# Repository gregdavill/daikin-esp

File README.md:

# Daikin-ESP

Wireless A/C Controller, an ESP32-C3 based hardware module to connect to a Daikin ducted A/C system and enable WiFi control in Home Assistant.

## Hardware

The PCB repo contains a few different designs:
 - `saphire-captain` : Initial ESP32 + XL1192 board. Power extraction from the bus and transmission didn't work well.
 - `hb-bob-r0.1` : Breakout board designed for the MAX22088 homebus transceiver. This board enabled rx/tx and power from the P1P2 bus.
 - `esp-daikin-r1.0` : Basic ESP32-C3 board with DCDC, dosigned to attach directly to the hb-bob board.

## Firmware

The current firmware targets the `esp-daikin` + `hb-bob` PCB combo. Initial flashing is done with a serial connection to the ESP32-C3. Once flashed OTA updates are supported.
The firmware makes use of esphome to provide the WiFi and Home Assistant code base. A simple C++ component is used to handle the low level encoding, and protocol level decoding.

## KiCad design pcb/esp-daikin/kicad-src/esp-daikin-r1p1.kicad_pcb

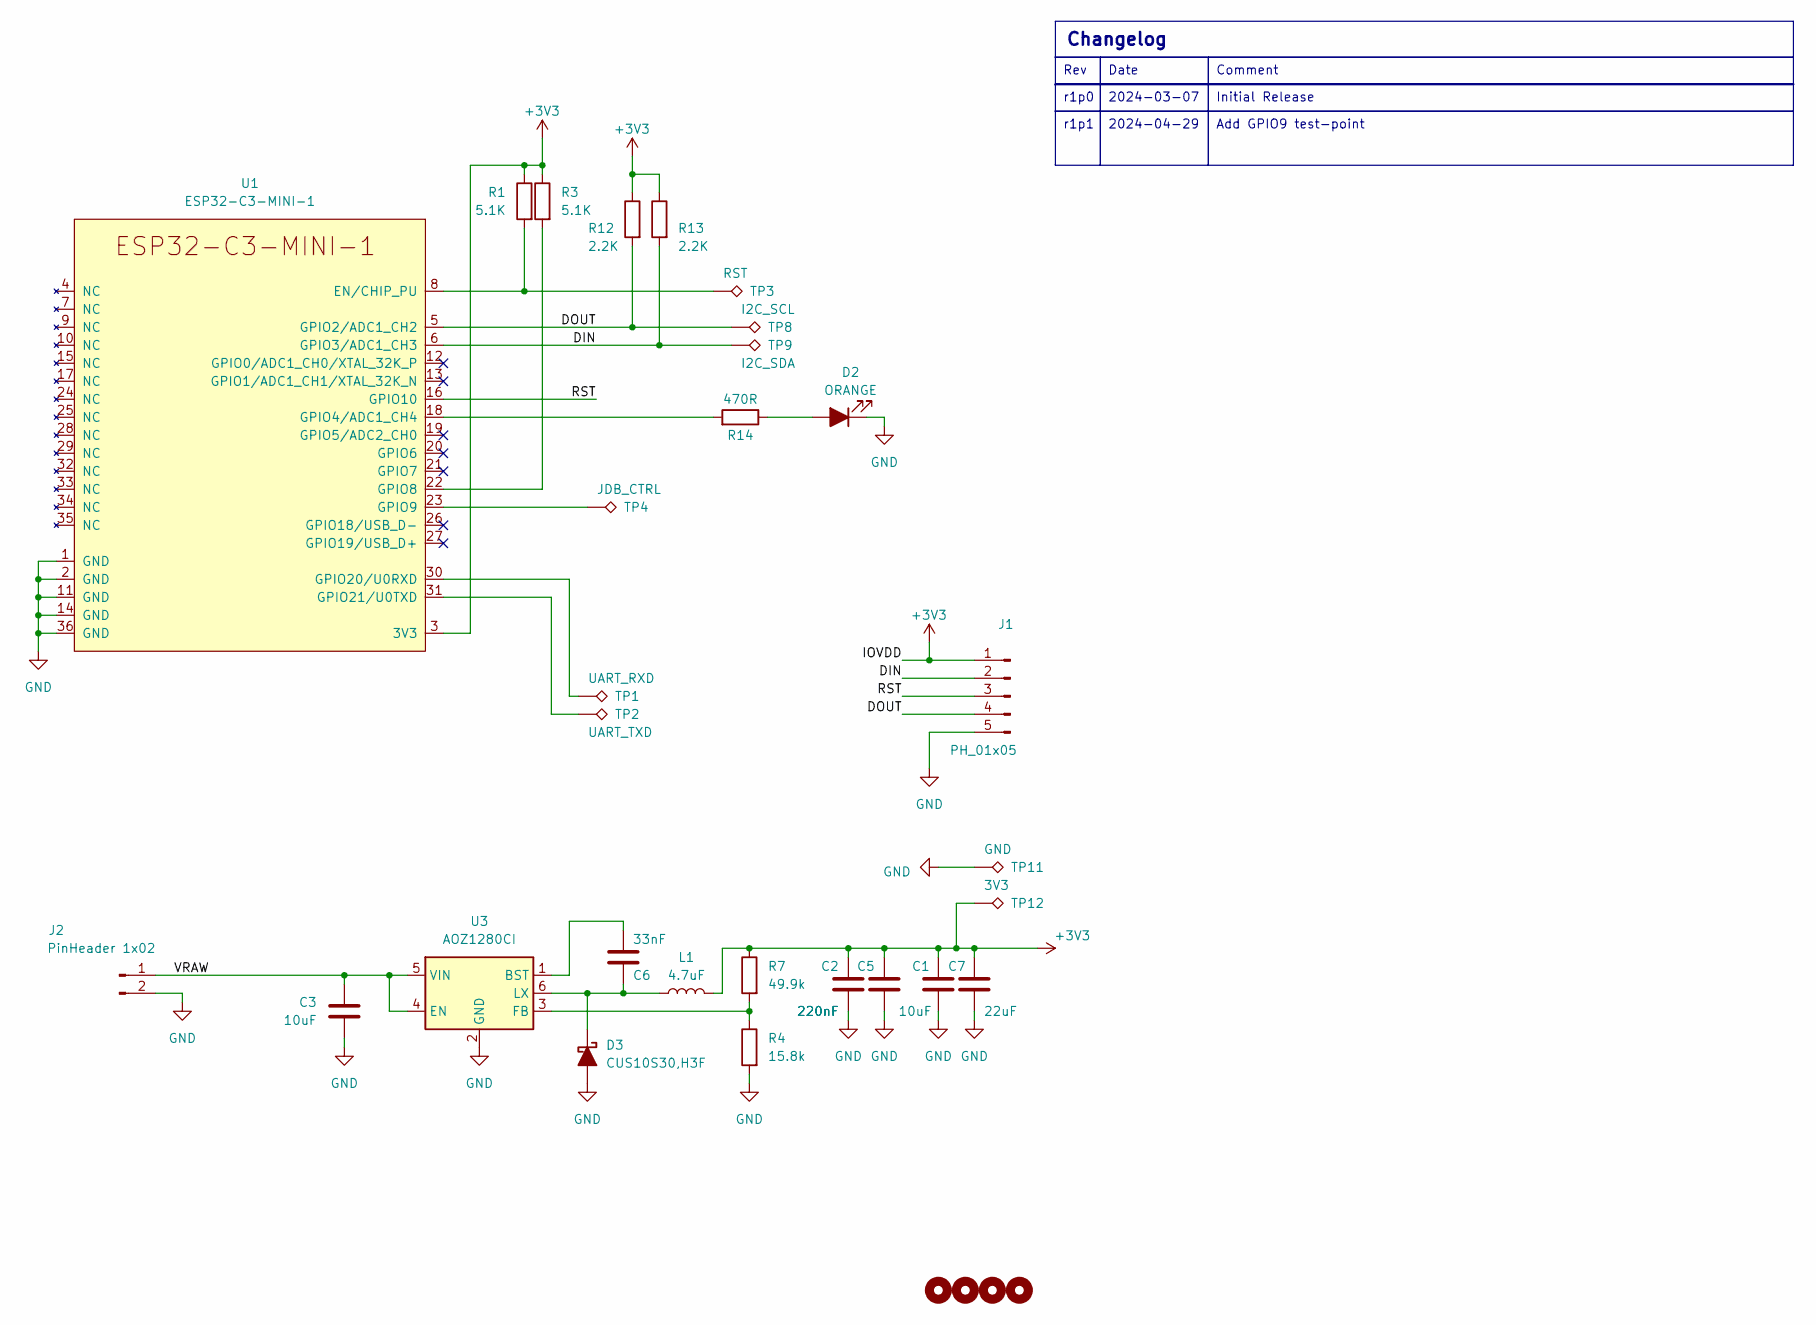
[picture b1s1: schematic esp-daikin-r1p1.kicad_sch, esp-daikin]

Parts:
C1, C3: 10uF; C_0603_1608Metric; LCSC C96446
C2, C5: 220nF; C_0402_1005Metric; LCSC C16772
C6: 33nF; C_0402_1005Metric; LCSC C106862
C7: 22uF; C_0603_1608Metric; LCSC C59461
D2: ORANGE; LED_0402_1005Metric; LCSC C965791
D3: CUS10S30,H3F; D_SOD-523; LCSC C8523
H1, H2, H3, H4: MountingHole; MountingHole_3.2mm_M3_DIN965
J1: PH_01x05; PinHeader_1x05_P2.54mm_Vertical
J2: PinHeader 1x02; PinHeader_1x02_P2.54mm_Vertical
L1: 4.7uF; L_0805_2012Metric; LCSC C63166
R1, R3: 5.1K; R_0402_1005Metric; LCSC C25905
R4: 15.8k; R_0402_1005Metric; LCSC C26956
R7: 49.9k; R_0402_1005Metric; LCSC C25897
R12, R13: 2.2K; R_0402_1005Metric; LCSC C25879
R14: 470R; R_0402_1005Metric; LCSC C25117
TP1: UART_RXD; TestPoint_Pad_D1.0mm
TP2: UART_TXD; TestPoint_Pad_D1.0mm
TP3: RST; TestPoint_Pad_D1.0mm
TP4: JDB_CTRL; TestPoint_Pad_D1.0mm
TP8: I2C_SCL; TestPoint_Pad_D1.0mm
TP9: I2C_SDA; TestPoint_Pad_D1.0mm
TP11: GND; TestPoint_Pad_D1.0mm
TP12: 3V3; TestPoint_Pad_D1.0mm
U1: ESP32-C3-MINI-1; LCSC C2934569
U3: AOZ1280CI; SOT-23-6; LCSC C41240

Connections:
+3V3: C1.1, C2.1, C5.1, C7.1, J1.1, L1.2, R1.1, R3.1, R7.1, R12.1, R13.1, TP12.1, U1.3 (3V3)
/DIN: J1.2, R13.2, TP9.1, U1.6 (GPIO3/ADC1_CH3)
/DOUT: J1.4, R12.2, TP8.1, U1.5 (GPIO2/ADC1_CH2)
/RST: J1.3, U1.16 (GPIO10)
/VRAW: C3.1, J2.1, U3.4 (EN), U3.5 (VIN)
GND: C1.2, C2.2, C3.2, C5.2, C7.2, D2.1 (K), D3.2 (A), J1.5, J2.2, R4.2, TP11.1, U1.1 (GND), U1.2 (GND), U1.11 (GND), U1.14 (GND), U1.36 (GND), U1.37 (GND), U1.38 (GND), U1.39 (GND), U1.40 (GND), U1.41 (GND), U1.42 (GND), U1.43 (GND), U1.44 (GND), U1.45 (GND), U1.46 (GND), U1.47 (GND), U1.48 (GND), U1.49 (GND), U1.50 (GND), U1.51 (GND), U1.52 (GND), U1.53 (GND), U3.2 (GND)
unnamed: D2.2 (A), R14.1
unnamed: C6.1, D3.1 (K), L1.1, U3.6 (LX)
unnamed: R1.2, TP3.1, U1.8 (EN/CHIP_PU)
unnamed: R14.2, U1.18 (GPIO4/ADC1_CH4)
unnamed: R3.2, U1.22 (GPIO8)
unnamed: TP4.1, U1.23 (GPIO9)
unnamed: TP1.1, U1.30 (GPIO20/U0RXD)
unnamed: TP2.1, U1.31 (GPIO21/U0TXD)
unnamed: C6.2, U3.1 (BST)
unnamed: R4.1, R7.2, U3.3 (FB)

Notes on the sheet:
Add GPIO9 test-point
Date
r1p0
Changelog
Rev
Comment
2024-03-07
2024-04-29
Initial Release
r1p1

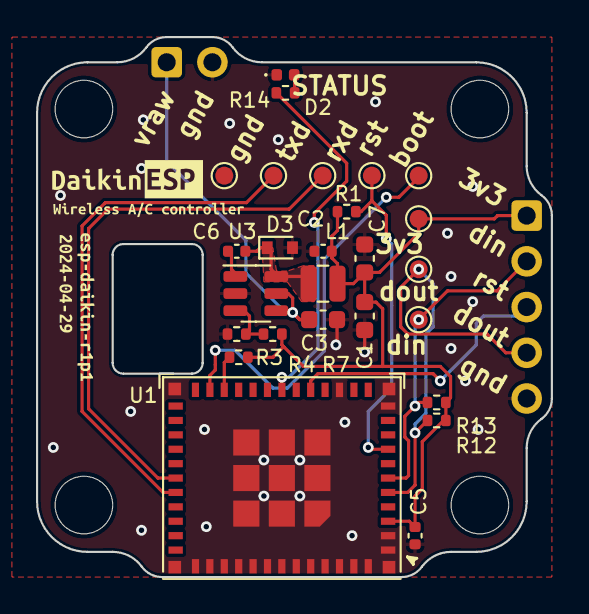
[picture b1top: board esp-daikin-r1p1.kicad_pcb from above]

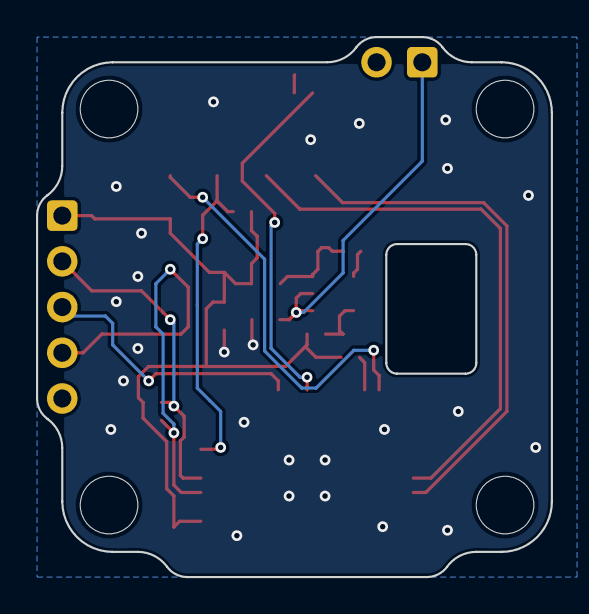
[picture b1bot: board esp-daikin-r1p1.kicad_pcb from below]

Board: 2 copper layers, 28.6 x 30.0 mm, 37 parts (6 on the bottom side), 16 nets.

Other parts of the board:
kibuzzard-65E1B0DF: G***; kibuzzard-65E1B0DF
kibuzzard-65E1B071: G***; kibuzzard-65E1B071
kibuzzard-65E1B080: G***; kibuzzard-65E1B080
kibuzzard-663027A7: G***; kibuzzard-663027A7
kibuzzard-663027CC: G***; kibuzzard-663027CC

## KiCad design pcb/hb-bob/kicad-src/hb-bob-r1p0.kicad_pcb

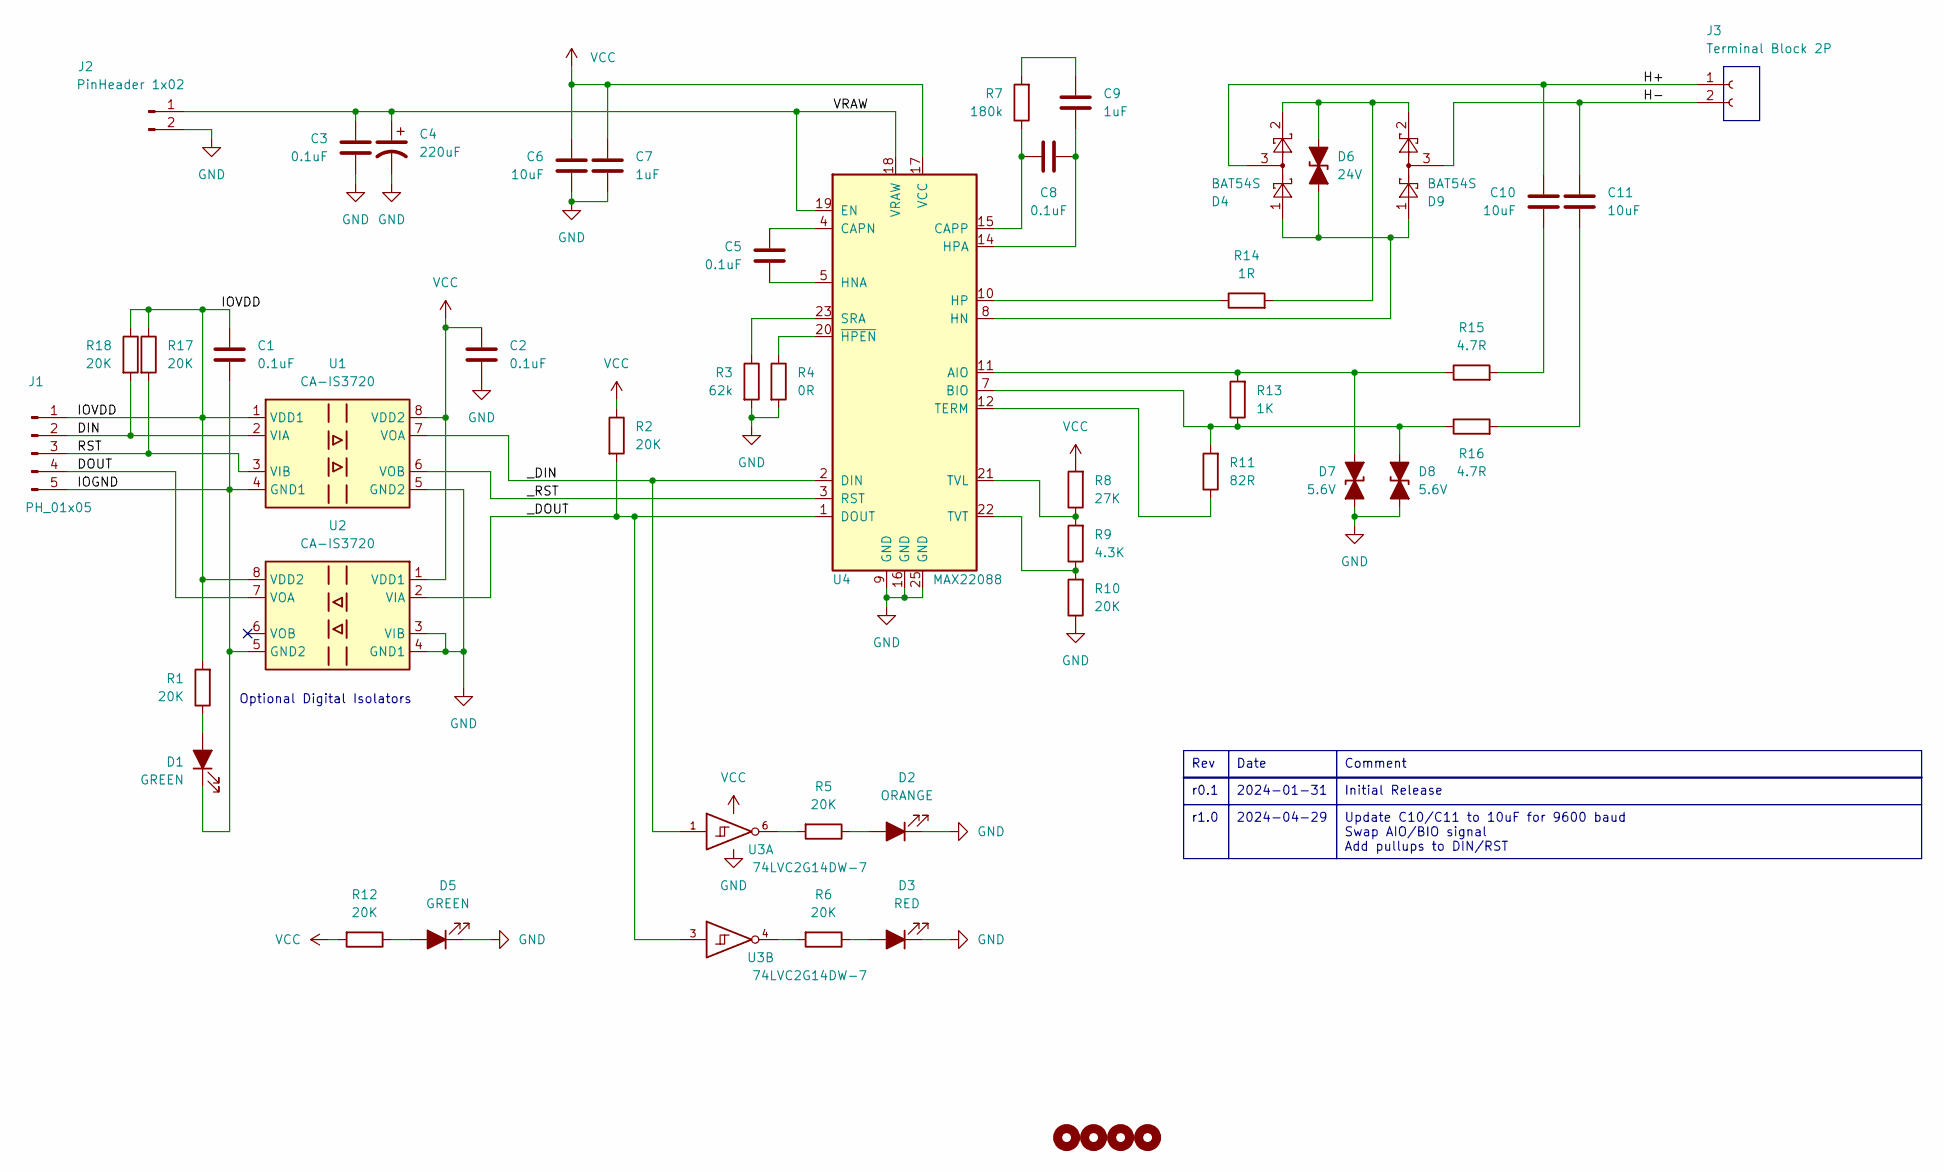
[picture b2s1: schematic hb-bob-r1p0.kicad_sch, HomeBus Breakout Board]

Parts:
C1, C2, C3, C5, C8: 0.1uF; C_0402_1005Metric; LCSC C1525
C4: 220uF; CP_Elec_6.3x7.7; LCSC C2918361
C6, C10, C11: 10uF; C_0402_1005Metric; LCSC C15525
C7, C9: 1uF; C_0402_1005Metric; LCSC C52923
D1, D5: GREEN; LED_0402_1005Metric; LCSC C165980
D2: ORANGE; LED_0402_1005Metric; LCSC C165980
D3: RED; LED_0402_1005Metric; LCSC C165980
D4, D9: BAT54S; SOT-23; LCSC C916425
D6: 24V; D_SOD-123F; LCSC C908212
D7, D8: 5.6V; D_SOD-923; LCSC C151980
H1, H2, H3, H4: MountingHole; MountingHole_3.2mm_M3_DIN965
J1: PH_01x05; PinHeader_1x05_P2.54mm_Vertical
J2: PinHeader 1x02; PinHeader_1x02_P2.54mm_Vertical
J3: Terminal Block 2P; PhoenixContact_MC_1,5_2-G-3.81_1x02_P3.81mm_Horizontal; LCSC C8387
R1, R2, R5, R6, R10, R12, R17, R18: 20K; R_0402_1005Metric; LCSC C25765
R3: 62k; R_0402_1005Metric; LCSC C37825
R4: 0R; R_0402_1005Metric; LCSC C60485
R7: 180k; R_0402_1005Metric; LCSC C25760
R8: 27K; R_0402_1005Metric; LCSC C25771
R9: 4.3K; R_0402_1005Metric; LCSC C25899
R11: 82R; R_0402_1005Metric; LCSC C2909389
R13: 1K; R_0402_1005Metric; LCSC C11702
R14: 1R; R_0805_2012Metric; LCSC C131397
R15, R16: 4.7R; R_0603_1608Metric; LCSC C137705
U1, U2: CA-IS3720; SOIC-8_3.9x4.9mm_P1.27mm; LCSC C428882
U3: 74LVC2G14DW-7; SOT-363_SC-70-6; LCSC C362110
U4: MAX22088; QFN-24-1EP_4x4mm_P0.5mm_EP2.6x2.6mm; LCSC C5258925

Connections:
/DIN: J1.2, R18.2, U1.2 (VIA)
/DOUT: J1.4, U2.7 (VOA)
/H+: C10.2, D4.3, J3.1
/H-: C11.2, D9.3, J3.2
/IOGND: C1.2, D1.1 (K), J1.5, U1.4 (GND1), U2.5 (GND2)
/IOVDD: C1.1, J1.1, R1.2, R17.1, R18.1, U1.1 (VDD1), U2.8 (VDD2)
/RST: J1.3, R17.2, U1.3 (VIB)
/VRAW: C3.1, C4.1, J2.1, U4.18 (VRAW), U4.19 (EN)
/_DIN: U1.7 (VOA), U3.1, U4.2 (DIN)
/_DOUT: R2.2, U2.2 (VIA), U3.3, U4.1 (DOUT)
/_RST: U1.6 (VOB), U4.3 (RST)
GND: C2.2, C3.2, C4.2, C6.2, C7.2, D2.1 (K), D3.1 (K), D5.1 (K), D7.2 (A2), D8.2 (A2), J2.2, R3.2, R4.2, R10.1, U1.5 (GND2), U2.3 (VIB), U2.4 (GND1), U3.2 (GND), U4.9 (GND), U4.16 (GND), U4.25 (GND)
unnamed: C9.1, R7.2
unnamed: C10.1, R15.2
unnamed: C11.1, R16.2
unnamed: D1.2 (A), R1.1
unnamed: D2.2 (A), R5.1
unnamed: D3.2 (A), R6.1
unnamed: D5.2 (A), R12.1
unnamed: D4.1, D6.1 (A1), D9.1, U4.8 (HN)
unnamed: D4.2, D6.2 (A2), D9.2, R14.2
unnamed: D7.1 (A1), R13.2, R15.1, U4.11 (AIO)
unnamed: D8.1 (A1), R11.2, R13.1, R16.1, U4.7 (BIO)
unnamed: R5.2, U3.6
unnamed: R6.2, U3.4
unnamed: C5.1, U4.4 (CAPN)
unnamed: C8.2, R7.1, U4.15 (CAPP)
unnamed: C5.2, U4.5 (HNA)
unnamed: R14.1, U4.10 (HP)
unnamed: C8.1, C9.2, U4.14 (HPA)
unnamed: R3.1, U4.23 (SRA)
unnamed: R11.1, U4.12 (TERM)
unnamed: R8.1, R9.2, U4.21 (TVL)
unnamed: R9.1, R10.2, U4.22 (TVT)
unnamed: R4.1, U4.20 (~HPEN)
VCC: C2.1, C6.1, C7.1, R2.1, R8.2, R12.2, U1.8 (VDD2), U2.1 (VDD1), U3.5 (VCC), U4.17 (VCC)

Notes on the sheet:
r0.1
2024-04-29
Initial Release
Update C10/C11 to 10uF for 9600 baud Swap AIO/BIO signal Add pullups to DIN/RST
Comment
Rev
2024-01-31
Date
r1.0
Optional Digital Isolators

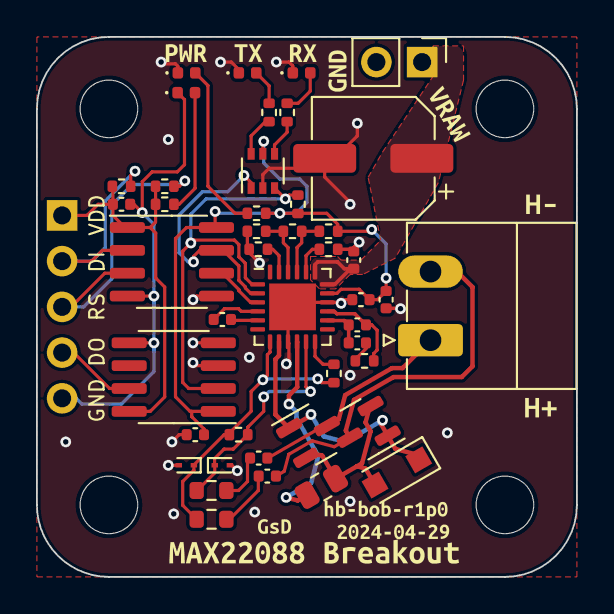
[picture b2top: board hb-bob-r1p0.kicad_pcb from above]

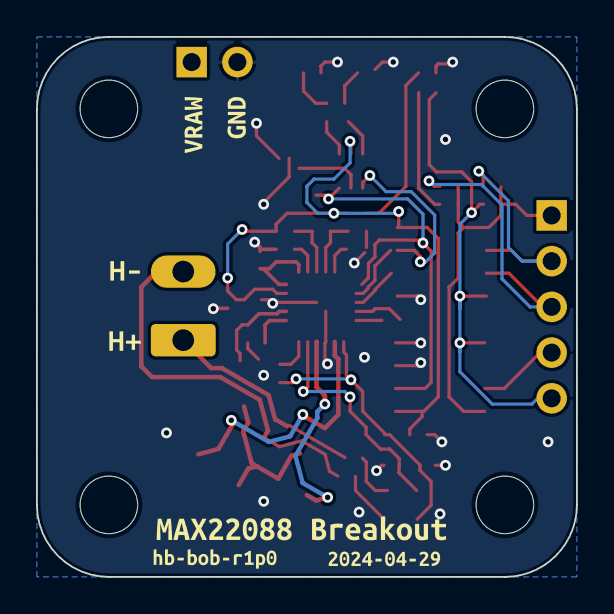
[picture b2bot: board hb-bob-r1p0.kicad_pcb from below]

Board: 2 copper layers, 30.0 x 30.0 mm, 67 parts (7 on the bottom side), 36 nets.

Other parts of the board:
kibuzzard-65B6C60D, kibuzzard-65B6C60D#2: G***; kibuzzard-65B6C60D
kibuzzard-65B6C61A, kibuzzard-65B6C61A#2: G***; kibuzzard-65B6C61A
kibuzzard-65B9E354: G***; kibuzzard-65B9E354
kibuzzard-65B62A1A, kibuzzard-65B62A1A#2: G***; kibuzzard-65B62A1A
kibuzzard-65B62B19, kibuzzard-65B62B19#2: G***; kibuzzard-65B62B19
kibuzzard-65B62B21, kibuzzard-65B62B21#2: G***; kibuzzard-65B62B21
kibuzzard-65B629C5: G***; kibuzzard-65B629C5
kibuzzard-65B629E6: G***; kibuzzard-65B629E6
kibuzzard-65B629EE: G***; kibuzzard-65B629EE
kibuzzard-662F7DF1: G***; kibuzzard-662F7DF1
kibuzzard-662F7DF9: G***; kibuzzard-662F7DF9
kibuzzard-662F7E09: G***; kibuzzard-662F7E09
kibuzzard-662F7E13: G***; kibuzzard-662F7E13

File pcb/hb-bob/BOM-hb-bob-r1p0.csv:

Comment,Designator,Footprint,LCSC
1K,R13,R_0402_1005Metric,C11702
1R,R14,R_0805_2012Metric,C131397
4.7R,"R15,R16",R_0603_1608Metric,C137705
5.6V,"D7,D8",D_SOD-923,C151980
0.1uF,"C1,C2,C3,C5,C8",C_0402_1005Metric,C1525
10uF,"C10,C11,C6",C_0402_1005Metric,C15525
GREEN,"D1,D2,D3,D5",LED_0402_1005Metric,C165980
180k,R7,R_0402_1005Metric,C25760
20K,"R1,R10,R12,R17,R18,R2,R5,R6",R_0402_1005Metric,C25765
27K,R8,R_0402_1005Metric,C25771
4.3K,R9,R_0402_1005Metric,C25899
82R,R11,R_0402_1005Metric,C2909389
220uF,C4,CP_Elec_6.3x7.7,C2918361
74LVC2G14DW-7,U3,SOT-363_SC-70-6,C362110
62k,R3,R_0402_1005Metric,C37825
CA-IS3720,"U1,U2",SOIC-8_3.9x4.9mm_P1.27mm,C428882
MAX22088,U4,QFN-24-1EP_4x4mm_P0.5mm_EP2.6x2.6mm,C5258925
1uF,"C7,C9",C_0402_1005Metric,C52923
0R,R4,R_0402_1005Metric,C60485
Terminal Block 2P,J3,"PhoenixContact_MC_1,5_2-G-3.81_1x02_P3.81mm_Horizontal",C8387
24V,D6,D_SOD-123F,C908212
BAT54S,"D4,D9",SOT-23,C916425
PH_01x05,J1,PinHeader_1x05_P2.54mm_Vertical,
PinHeader 1x02,J2,PinHeader_1x02_P2.54mm_Vertical,

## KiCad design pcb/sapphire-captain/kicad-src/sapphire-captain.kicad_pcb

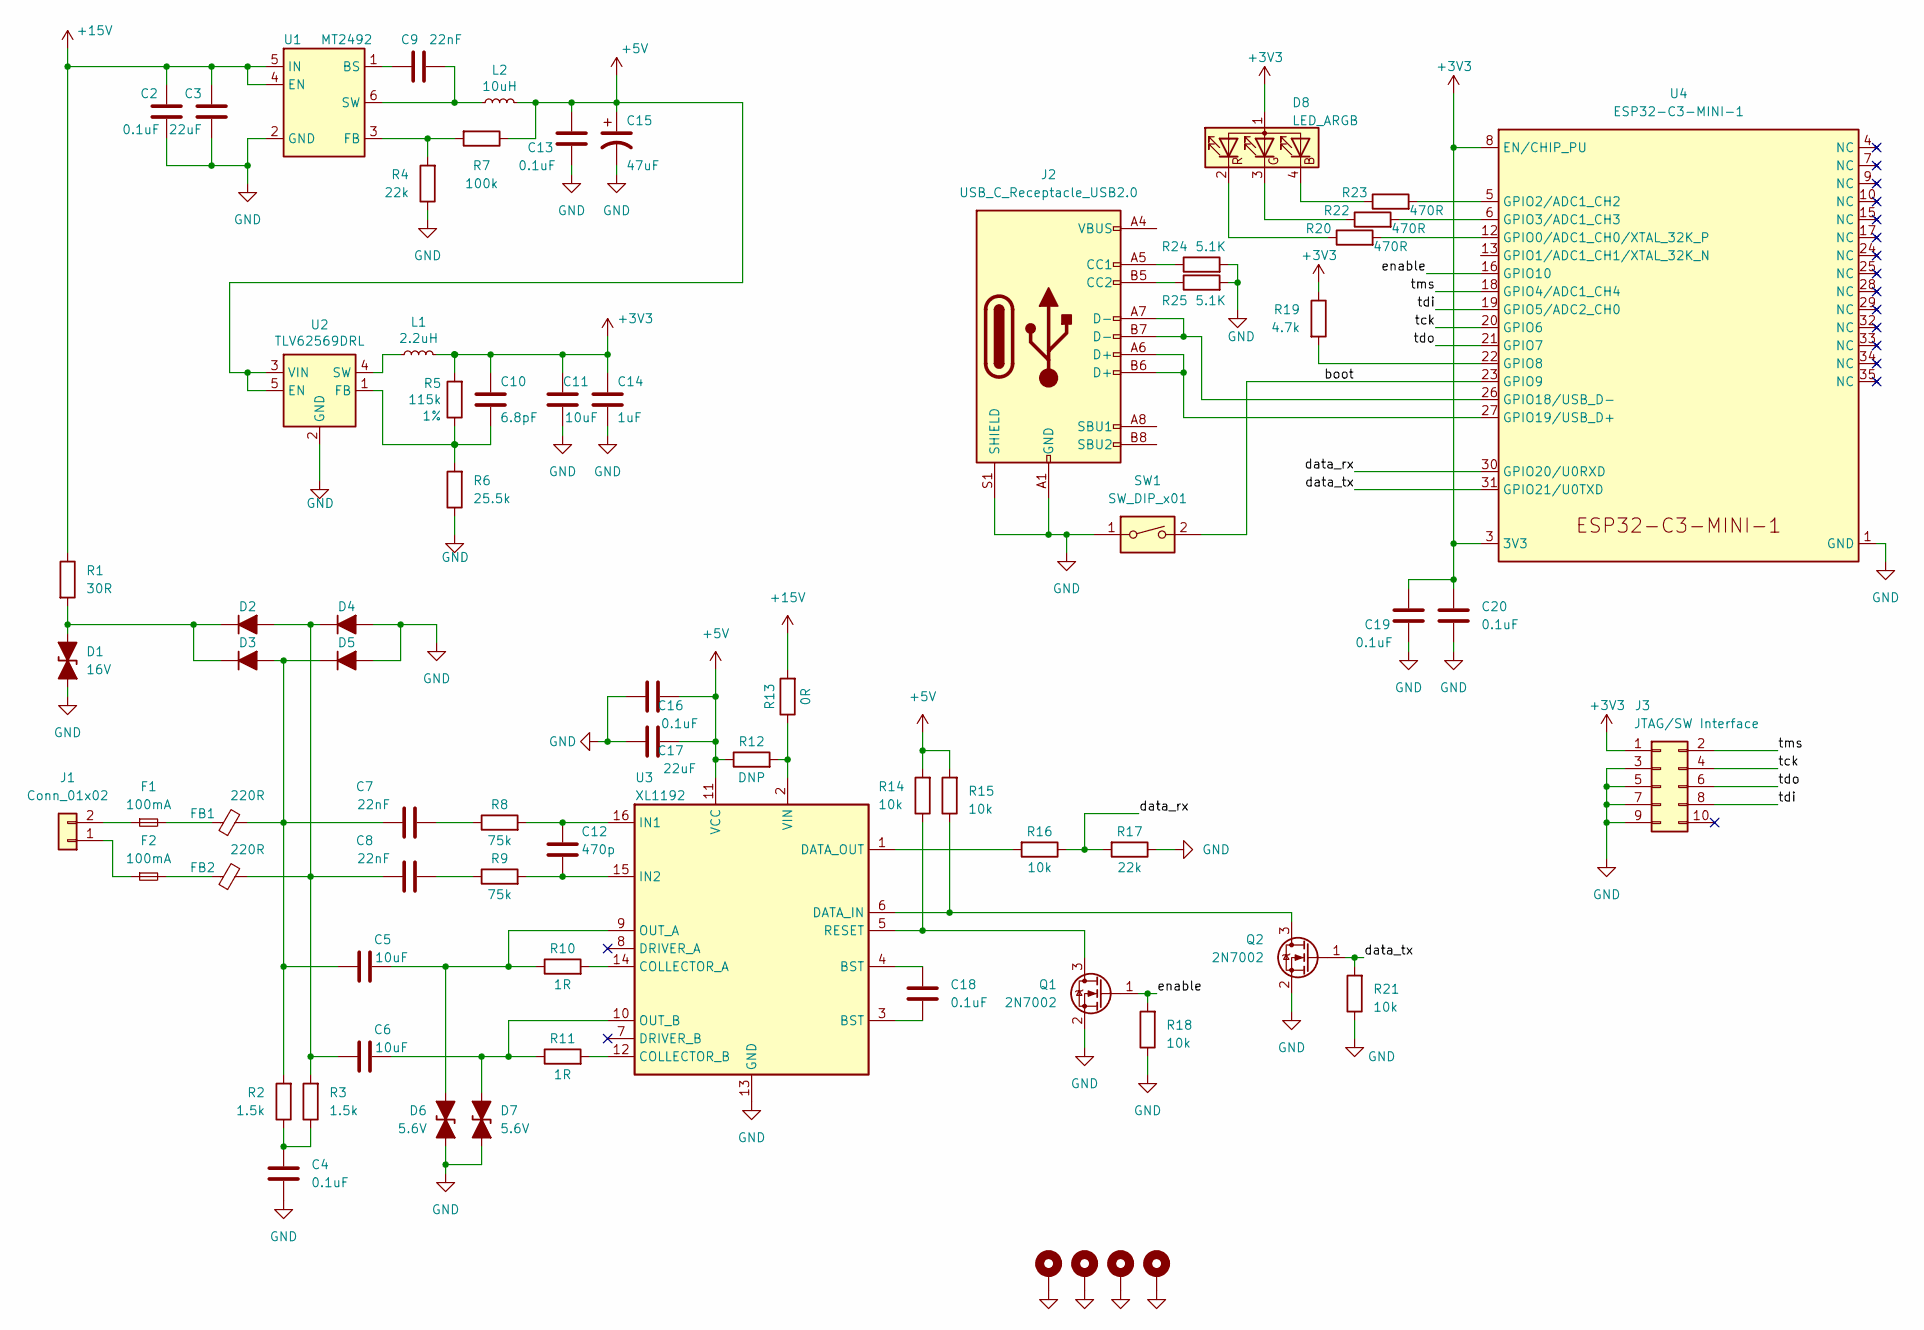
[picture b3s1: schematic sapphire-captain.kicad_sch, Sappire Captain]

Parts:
C2, C4, C13, C16, C18, C19, C20: 0.1uF; C_0402_1005Metric
C3: 22uF; C_1206_3216Metric
C5, C6, C11: 10uF; C_0603_1608Metric
C7, C8, C9: 22nF; C_0402_1005Metric
C10: 6.8pF; C_0402_1005Metric
C12: 470p; C_0402_1005Metric
C14: 1uF; C_0402_1005Metric
C15: 47uF; CP_Elec_6.3x4.5; lcsc C72522
C17: 22uF; C_0805_2012Metric
D1: 16V; D_SOD-123F
D2, D3, D4, D5: D_Filled; D_SOD-123F
D6, D7: 5.6V; D_SOD-123F
D8: LED_ARGB; 0404LED_RGB
F1, F2: 100mA; Fuse_0402_1005Metric
FB1, FB2: 220R; L_0402_1005Metric
H1, H2, H3, H4: MountingHole_Pad; MountingHole_3.2mm_M3_Pad_Via
J1: Conn_01x02; TerminalBlock_WAGO_236-102_1x02_P5.00mm_45Degree
J2: USB_C_Receptacle_USB2.0; USB_C_Receptacle_XKB_U262-16XN-4BVC11
J3: JTAG/SW Interface; PinHeader_2x05_P1.27mm_Vertical_SMD
L1: 2.2uH; L_Taiyo-Yuden_NR-30xx
L2: 10uH; L_Taiyo-Yuden_NR-30xx; lcsc C340363
Q1, Q2: 2N7002; SOT-23
R1: 30R; R_2010_5025Metric
R2, R3: 1.5k; R_0402_1005Metric
R4, R17: 22k; R_0402_1005Metric
R5: 115k; R_0402_1005Metric
R6: 25.5k; R_0402_1005Metric
R7: 100k; R_0402_1005Metric
R8, R9: 75k; R_0402_1005Metric
R10, R11: 1R; R_0805_2012Metric
R12: DNP; R_0402_1005Metric
R13: 0R; R_0402_1005Metric
R14, R15, R16, R18, R21: 10k; R_0402_1005Metric
R19: 4.7k; R_0402_1005Metric
R20, R22, R23: 470R; R_0402_1005Metric
R24, R25: 5.1K; R_0402_1005Metric
SW1: SW_DIP_x01; SW_SPST_PTS810
U1: MT2492; SOT-23-6
U2: TLV62569DRL; SOT-666
U3: XL1192; SO-16_3.9x9.9mm_P1.27mm
U4: ESP32-C3-MINI-1

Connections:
+3V3: C10.1, C11.1, C14.1, C19.1, C20.1, D8.1 (A), J3.1, L1.2, R5.2, R19.1, U4.3 (3V3), U4.8 (EN/CHIP_PU)
+5V: C13.1, C15.1, C16.2, C17.2, L2.2, R7.1, R12.1, R14.2, R15.2, U2.3 (VIN), U2.5 (EN), U3.11 (VCC)
+15V: C2.1, C3.1, R1.1, R13.2, U1.4 (EN), U1.5 (IN)
/boot: SW1.2, U4.23 (GPIO9)
/data_rx: R16.1, R17.2, U4.30 (GPIO20/U0RXD)
/data_tx: Q2.1 (G), R21.2, U4.31 (GPIO21/U0TXD)
/enable: Q1.1 (G), R18.2, U4.16 (GPIO10)
/tck: J3.4, U4.20 (GPIO6)
/tdi: J3.8, U4.19 (GPIO5/ADC2_CH0)
/tdo: J3.6, U4.21 (GPIO7)
/tms: J3.2, U4.18 (GPIO4/ADC1_CH4)
GND: C2.2, C3.2, C4.1, C11.2, C13.2, C14.2, C15.2, C16.1, C17.1, C19.2, C20.2, D1.2 (A2), D4.2 (A), D5.2 (A), D6.1 (A1), D7.1 (A1), H1.1, H2.1, H3.1, H4.1, J2.A1 (GND), J2.A12 (GND), J2.B1 (GND), J2.B12 (GND), J2.S1 (SHIELD), J3.3, J3.5, J3.7, J3.9, Q1.2 (S), Q2.2 (S), R4.1, R6.1, R17.1, R18.1, R21.1, R24.2, R25.2, SW1.1, U1.2 (GND), U2.2 (GND), U3.13 (GND), U4.1 (GND), U4.2 (GND), U4.36 (GND), U4.37 (GND), U4.38 (GND), U4.39 (GND), U4.40 (GND), U4.41 (GND), U4.42 (GND), U4.43 (GND), U4.44 (GND), U4.45 (GND), U4.46 (GND), U4.47 (GND), U4.48 (GND), U4.49 (GND), U4.50 (GND), U4.51 (GND), U4.52 (GND), U4.53 (GND)
unnamed: C4.2, R2.1, R3.1
unnamed: C7.2, R8.1
unnamed: C8.2, R9.1
unnamed: D1.1 (A1), D2.1 (K), D3.1 (K), R1.2
unnamed: C6.1, C8.1, D2.2 (A), D4.1 (K), FB2.2, R3.2
unnamed: C5.1, C7.1, D3.2 (A), D5.1 (K), FB1.2, R2.2
unnamed: C5.2, D6.2 (A2), R10.1, U3.9 (OUT_A)
unnamed: C6.2, D7.2 (A2), R11.1, U3.10 (OUT_B)
unnamed: D8.4 (BK), R23.1
unnamed: D8.3 (GK), R22.1
unnamed: D8.2 (RK), R20.1
unnamed: F1.2, FB1.1
unnamed: F2.2, FB2.1
unnamed: F2.1, J1.1
unnamed: F1.1, J1.2
unnamed: J2.A5 (CC1), R24.1
unnamed: J2.B5 (CC2), R25.1
unnamed: J2.A6 (D+), J2.B6 (D+), U4.27 (GPIO19/USB_D+)
unnamed: J2.A7 (D-), J2.B7 (D-), U4.26 (GPIO18/USB_D-)
unnamed: J2.A4 (VBUS), J2.A9 (VBUS), J2.B4 (VBUS), J2.B9 (VBUS)
unnamed: Q1.3 (D), R14.1, U3.5 (RESET)
unnamed: Q2.3 (D), R15.1, U3.6 (DATA_IN)
unnamed: C9.1, U1.1 (BS)
unnamed: R4.2, R7.2, U1.3 (FB)
unnamed: C9.2, L2.1, U1.6 (SW)
unnamed: C10.2, R5.1, R6.2, U2.1 (FB)
unnamed: L1.1, U2.4 (SW)
unnamed: C18.1, U3.4 (BST)
unnamed: C18.2, U3.3 (BST)
unnamed: R10.2, U3.14 (COLLECTOR_A)
unnamed: R11.2, U3.12 (COLLECTOR_B)
unnamed: R16.2, U3.1 (DATA_OUT)
unnamed: C12.1, R8.2, U3.16 (IN1)
unnamed: C12.2, R9.2, U3.15 (IN2)
unnamed: R12.2, R13.1, U3.2 (VIN)
unnamed: R20.2, U4.12 (GPIO0/ADC1_CH0/XTAL_32K_P)
unnamed: R23.2, U4.5 (GPIO2/ADC1_CH2)
unnamed: R22.2, U4.6 (GPIO3/ADC1_CH3)
unnamed: R19.2, U4.22 (GPIO8)

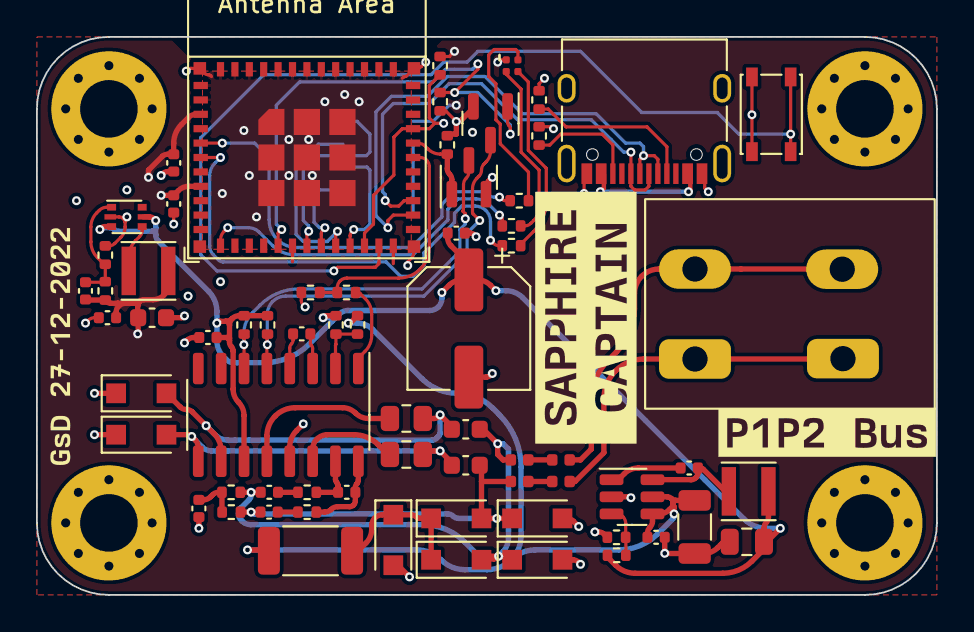
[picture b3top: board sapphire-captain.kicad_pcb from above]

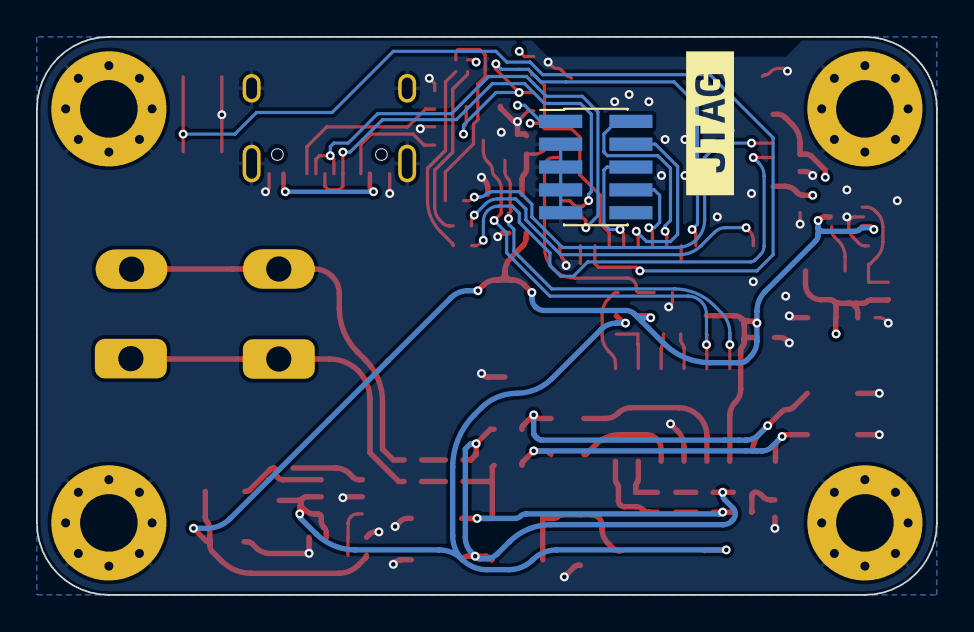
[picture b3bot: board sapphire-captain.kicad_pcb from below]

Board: 4 copper layers, 50.0 x 31.0 mm, 77 parts (2 on the bottom side), 51 nets.

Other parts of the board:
kibuzzard-63AA5C76: G***; kibuzzard-63AA5C76
kibuzzard-63AA625E: G***; kibuzzard-63AA625E
kibuzzard-63AA640E: G***; kibuzzard-63AA640E
kibuzzard-63AA6405: G***; kibuzzard-63AA6405
kibuzzard-63AA6611: G***; kibuzzard-63AA6611

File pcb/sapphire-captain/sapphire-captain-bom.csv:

Item,Qty,Reference(s),Value,LibPart,Footprint,Datasheet,MFG,Mfg,PN,PN-alt0,Tol,lcsc
21,7,"C2, C4, C13, C16, C18, C19, C20",0.1uF,Device:C,Capacitor_SMD:C_0402_1005Metric,~,Samsung Electro-Mechanics,Yageo,CL05B104KO5NNNC,,,
3,1,C3,22uF,Device:C,Capacitor_SMD:C_1206_3216Metric,~,Samsung Electro-Mechanics,Yageo,CL31A226KAHNNNE,,,
9,3,"C5, C6, C11",10uF,Device:C,Capacitor_SMD:C_0603_1608Metric,~,Samsung Electro-Mechanics,Yageo,CL10A106KP8NNNC,,,
9,3,"C7, C8, C9",22nF,Device:C,Capacitor_SMD:C_0402_1005Metric,~,Samsung Electro-Mechanics,Yageo,CL05B223KB5VPNC,,,
3,1,C10,6.8pF,Device:C,Capacitor_SMD:C_0402_1005Metric,~,Samsung Electro-Mechanics,Yageo,CC0402CRNPO9BN6R8,,,
3,1,C12,470p,Device:C,Capacitor_SMD:C_0402_1005Metric,~,Samsung Electro-Mechanics,,CL05B471KB5NNNC,,,
3,1,C14,1uF,Device:C,Capacitor_SMD:C_0402_1005Metric,~,Samsung Electro-Mechanics,Yageo,CL05X105KA5NQNC,,,
3,1,C15,47uF,Device:C_Polarized_US,Capacitor_SMD:CP_Elec_6.3x4.5,~,DMBJ,,RVT1V470M0605,ROQANG ,,C72522
3,1,C17,22uF,Device:C,Capacitor_SMD:C_0805_2012Metric,~,Samsung Electro-Mechanics,,CL21A226MAYNNNE,,,
3,1,D1,16V,Device:D_TVS_Filled,Diode_SMD:D_SOD-123F,~,,,"BZT52H-C16,115",,,
12,4,"D2, D3, D4, D5",D_Filled,Device:D_Filled,Diode_SMD:D_SOD-123F,~,Shandong Jingdao Microelectronics,,1N5819W,,,
6,2,"D6, D7",5.6V,Device:D_TVS_Filled,Diode_SMD:D_SOD-123F,~,,,"BZT52H-B5V6,115",,,
3,1,D8,LED_ARGB,Device:LED_ARGB,lib:0404LED_RGB,~,,,,,,
6,2,"F1, F2",100mA,Device:Fuse_Small,Fuse:Fuse_0402_1005Metric,~,Shenzhen JDT Fuse,,JFC0402-0250FS,,,
6,2,"FB1, FB2",220R,Device:FerriteBead_Small,Inductor_SMD:L_0402_1005Metric,~,Chilisin Elec,,PBY100505T-101Y-N,,,
3,1,J1,Conn_01x02,Connector_Generic:Conn_01x02,TerminalBlock_WAGO:TerminalBlock_WAGO_236-102_1x02_P5.00mm_45Degree,~,WAGO Corporation,,2604-1102,,,
3,1,J2,USB_C_Receptacle_USB2.0,Connector:USB_C_Receptacle_USB2.0,Connector_USB:USB_C_Receptacle_XKB_U262-16XN-4BVC11,https://www.usb.org/sites/default/files/documents/usb_type-c.zip,,,,,,
3,1,J3,JTAG/SW Interface,Connector_Generic:Conn_02x05_Odd_Even,Connector_PinHeader_1.27mm:PinHeader_2x05_P1.27mm_Vertical_SMD,~,,,,,,
3,1,L1,2.2uH,Device:L_Small,Inductor_SMD:L_Taiyo-Yuden_NR-30xx,~,,MINGSTAR ,UT252010N-2R2M,,,
3,1,L2,10uH,Device:L_Small,Inductor_SMD:L_Taiyo-Yuden_NR-30xx,~,YJYCOIN,,YNR3015-100M,,,C340363
6,2,"Q1, Q2",2N7002,Device:Q_NMOS_GSD,Package_TO_SOT_SMD:SOT-23,~,"Jiangsu Changjing Electronics Technology Co., Ltd.",,2N7002,,,
3,1,R1,30R,Device:R,Resistor_SMD:R_2010_5025Metric,~,YAGEO,,RC2010JK-0730RL,,,
6,2,"R2, R3",1.5k,Device:R,Resistor_SMD:R_0402_1005Metric,~,YAGEO,,RC0402FR-071K5L,,,
6,2,"R4, R17",22k,Device:R,Resistor_SMD:R_0402_1005Metric,~,YAGEO,Yageo,RC0402FR-0722KL,,,
3,1,R5,115k,Device:R,Resistor_SMD:R_0402_1005Metric,~,YAGEO,Yageo,RC0402FR-07115KL,,1%,
3,1,R6,25.5k,Device:R,Resistor_SMD:R_0402_1005Metric,~,YAGEO,Yageo,RC0402FR-0725K5L,,,
3,1,R7,100k,Device:R,Resistor_SMD:R_0402_1005Metric,~,YAGEO,Yageo,RC0402FR-07100KL,,1%,
6,2,"R8, R9",75k,Device:R,Resistor_SMD:R_0402_1005Metric,~,YAGEO,,RC0402FR-0775KL,,,
6,2,"R10, R11",1R,Device:R,Resistor_SMD:R_0805_2012Metric,~,YAGEO,,RC0805FR-071RL,,,
3,1,R12,DNP,Device:R,Resistor_SMD:R_0402_1005Metric,~,YAGEO,,,,,
3,1,R13,0R,Device:R,Resistor_SMD:R_0402_1005Metric,~,YAGEO,,RC0402FR-070RL,,,
15,5,"R14, R15, R16, R18, R21",10k,Device:R,Resistor_SMD:R_0402_1005Metric,~,YAGEO,,RC0402FR-0710KL,,,
3,1,R19,4.7k,Device:R,Resistor_SMD:R_0402_1005Metric,~,YAGEO,,RC0402FR-074K7L,,,
9,3,"R20, R22, R23",470R,Device:R,Resistor_SMD:R_0402_1005Metric,~,YAGEO,,RC0402FR-07470RL,,,
6,2,"R24, R25",5.1K,Device:R,Resistor_SMD:R_0402_1005Metric,~,YAGEO,,RC0402FR-075K1L,,,
3,1,SW1,SW_DIP_x01,Switch:SW_DIP_x01,Button_Switch_SMD:SW_SPST_PTS810,~,C&K,,PTS810SJK250SMTRLFS,,,
3,1,U1,MT2492,lib:MT2492,Package_TO_SOT_SMD:SOT-23-6,https://datasheet.lcsc.com/lcsc/1810262207_XI-AN-Aerosemi-Te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,XI'AN Aerosemi Tech,,MT2492,,,
3,1,U2,TLV62569DRL,Regulator_Switching:TLV62569DRL,Package_TO_SOT_SMD:SOT-666,http://www.ti.com/lit/ds/symlink/tlv62569.pdf,Texas Instruments,Texas Instruments,TLV62569DRLR,,,
3,1,U3,XL1192,sapphire-captain:XL1192,Package_SO:SO-16_3.9x9.9mm_P1.27mm,,XLSEMI,,XL1192S,,,
3,1,U4,ESP32-C3-MINI-1,Espressif:ESP32-C3-MINI-1,Espressif:ESP32-C3-MINI-1,https://www.espressif.com/sites/default/files/documentation/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,,,,,,

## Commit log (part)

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2024-04-28 doc: Add initial readme
2024-04-28 ref: Add XL1192 datasheet
2024-04-28 pcb: Update gitignore
2024-04-28 pcb: Add sapphire-captain production files
2024-04-28 pcb: Add sapphire-captain designs
    pcb: Update sapphire captain
2024-04-28 pcb: Add hb-bob designs
2024-04-28 pcb: Add hb-bob production files
2024-04-28 pcb: Add esp-daikin designs
2024-04-28 pcb: Add esp-daikin production files
2024-04-28 fw: Add initial esphome component
2024-04-28 doc: Update readme
2024-04-29 pcb: Update hb-bob
    - Update PN for C10/C11 to support 9600 baud
    - Swap AIO/BIO signals
    - Add pullups to external DIN/RST pins
2024-04-29 pcb: Add hb-bob-r1p0 production files
2024-04-29 pcb: Move esp-daikin folder
2024-04-29 pcb: Update daikin-esp
    - Add test-point for GPIO9
2024-04-29 pcb: Update daikin-esp schematic version
2024-04-29 pcb: Flip daikin-esp design
2024-04-29 pcb: Update kicad library paths
2024-04-29 pcb.esp-daikin: Update PNs
2024-04-29 pcb.esp-daikin: Rename files
2024-10-07 fw: Add template fan control
2024-10-07 pcb.daikin-esp: Add r1p1
    - Add GPIO9 test-point to enter UART boot
2024-10-10 fw: Update template fan from A/C on_state.
2024-10-10 fw: Fix issue where packet may become corrupt
2024-10-10 fw: Set config logging level to VERY_VERBOSE
2024-10-13 pcb.daikin-esp: Update production files to r1p1
2024-11-02 fw: Update debugging logs
2024-11-03 fw: Enable captive WiFi portal
2024-11-04 fw: Stop fan_speed changes from altering mode
2025-02-09 fw: Remove ducted fan template
2025-02-09 fw: Add extra temperature sensors
2025-02-09 ci: Add github CI build
2025-04-08 mech: Add 3d prints
2026-01-31 fix(pcb): fix C3 part number
    fixes #3
2026-02-07 feat: update RMT to idf 5.x API
2026-02-07 chore: update CONFIG_SCHEMA
2026-02-07 fix: Configure DaikinClimate as a component
2026-02-07 feat: add git describe diagnostic
2026-02-07 chore: Remove countSetBits
2026-02-07 feat: Refactor core logic with named types
2026-02-07 fix: ensure temperature is syncronised with homebus interface
2026-02-07 feat: Add extra seperate AC/FAN interfaces for homekit
2026-02-07 feat: double buffer rmt_rx
2026-02-07 fix: Set CLIMATE_ACTION_OFF on homekit interface when in unsupported modes
2026-02-07 chore: Tidy and refactor component
2026-02-07 feat: enable configurable P1P2 io
2026-02-07 feat: add filter status
2026-02-09 fix: Ignore strapping pin warning on TX GPIO
    https://esphome.io/guides/faq/#why-am-i-getting-a-warning-about-strapping-pins
2026-02-09 fix: Move to add_feature_flags
    Avoids these warnings:
    daikin_ducted.cpp:564:46: warning: 'void esphome::climate::ClimateTraits::set_supports_current_temperature(bool)'
    is deprecated: This method is deprecated, use add_feature_flags() instead
    The API reference shows what to do instead:
    https://api-docs.esphome.io/climate__traits_8h_source#l00132
2026-02-10 fix: erroneous mode change when handling CLIMATE_MODE::OFF
2026-04-07 feat: Acknowledge the 0x31 packet
    - With a remote attached it can go out of sync if the 0x31 is not ACK'd
    fixes gregdavill/daikin-esp#13
2026-04-07 fix: Include esp_driver_rmt for ESPHome 2026.3.x compatibility
    ESPHome 2026.3.x excludes esp_driver_rmt by default to speed up builds.
    Re-include it since homebus_rmt uses the ESP-IDF RMT driver directly.
2026-04-09 fix: bounds check in RMT decoder
2026-04-09 fix: Use bounded timeout for rmt_tx_wait_all_done
2026-04-09 fix: Bound unit name log to packet length
2026-04-09 fix: Add bounds check in send_simple_response
2026-04-09 fix: Handle temperature setpoint in AUTO mode
2026-04-09 style: Fix inconsistent brace/spacing in mode check
2026-04-09 refactor: Extract AUX_CHANGED_FLAG as protocol-level constant
2026-04-09 fix: Read fan speed from mode-appropriate register
    Read from HEATING_FAN_SPEED when in HEAT mode instead of always reading
    from COOLING_FAN_SPEED, which may not reflect the active fan speed.
2026-04-09 refactor: Replace magic numbers with named constants for counter/alarm
2026-04-09 refactor: Rename reserved_N fields to unknown_N in ControlResponse
2026-04-09 chore: update ci checkout to v6
2026-04-11 fix: Make RMT TX non-blocking to prevent RX framing errors
    write_bytes() was blocking the main loop. A framing error may be
    produced when RX packet is processed during transmission.
    Blocking delay/wait updated with a queued TX state machine and ISR
    callback for completion notification.
    Fixes #7
2026-04-19 ci: Use esphome github action and pin to 2026.4.0
    Use the github action whcih runs the build inside a docker container for faster
    builds. Pin to a fixed version for reproducible builds.
    Upload firmware artifact that can be flashed to a device.
